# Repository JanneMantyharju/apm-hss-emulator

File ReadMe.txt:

This repository contains sources for Ardupilot Mega to Hitec telemetry adapter
For more information see: http://wp.me/p12J9M-3M

Files in this repository:
adapter/ - Source files, compile with Arduino
libraries/ - Mavlink and support libraries
hss.sch - Schematics in Eagle format
hss.brd - Board in Eagle format

Compile to ATMega328p with 8MHz clock setting.

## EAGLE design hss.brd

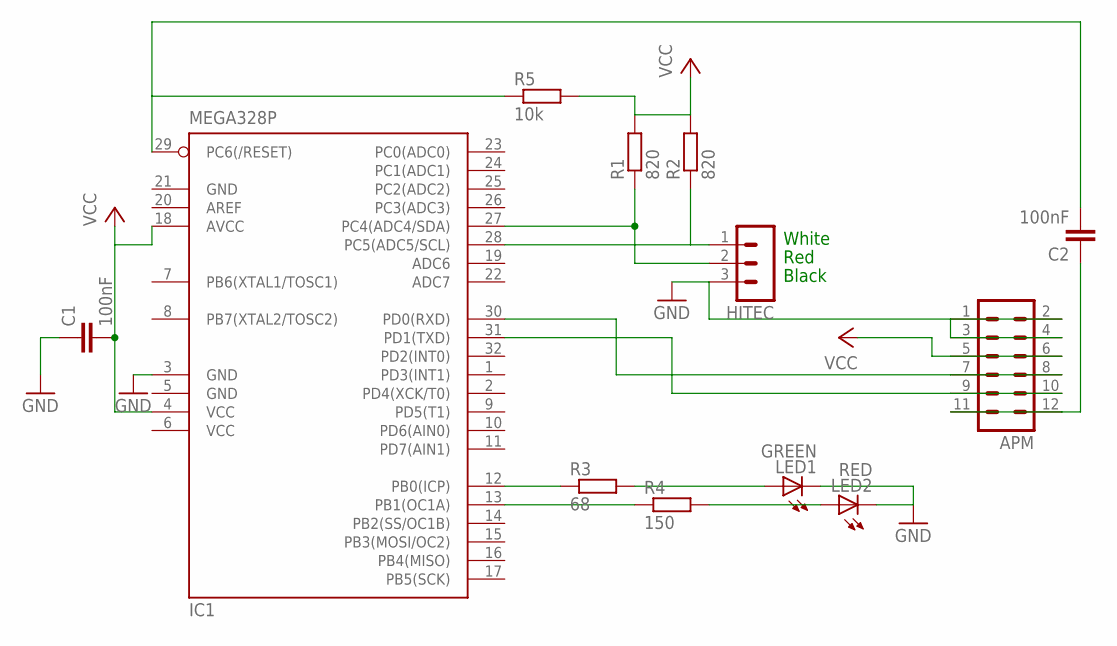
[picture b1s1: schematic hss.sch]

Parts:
APM: MA06-2
C1, C2: 100nF; C1206
HITEC: MA03-1
IC1: MEGA328P; TQFP32-08
LED1: GREEN; 1206
LED2: RED; 1206
R1, R2: 820; M1206
R3: 68; M1206
R4: 150; M1206
R5: 10k; M1206

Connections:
GND: APM.1, APM.2, APM.3, APM.4, C1.1, HITEC.3, IC1.3 (GND), IC1.5 (GND), IC1.21 (GND), LED1.C, LED2.C
unnamed: IC1.12 (PB0(ICP)), R3.1
unnamed: HITEC.2, IC1.27 (PC4(ADC4/SDA)), R1.1
unnamed: HITEC.1, IC1.28 (PC5(ADC5/SCL)), R2.1
unnamed: C2.2, IC1.29 (PC6(/RESET)), R5.1
unnamed: LED1.A, R3.2
unnamed: IC1.13 (PB1(OC1A)), R4.1
unnamed: LED2.A, R4.2
unnamed: APM.11, APM.12, C2.1
unnamed: APM.9, APM.10, IC1.31 (PD1(TXD))
unnamed: APM.7, APM.8, IC1.30 (PD0(RXD))
VCC: APM.5, APM.6, C1.2, IC1.4 (VCC), IC1.6 (VCC), IC1.18 (AVCC), R1.2, R2.2, R5.2

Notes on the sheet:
White
Red
Black

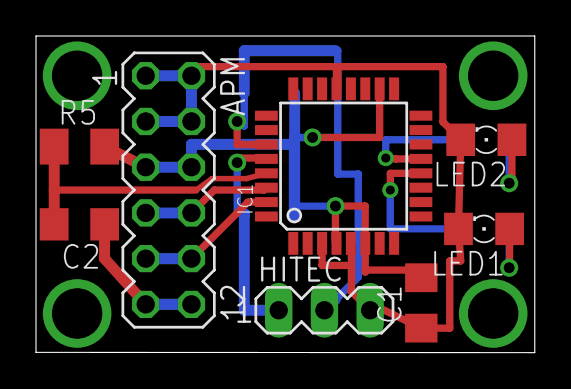
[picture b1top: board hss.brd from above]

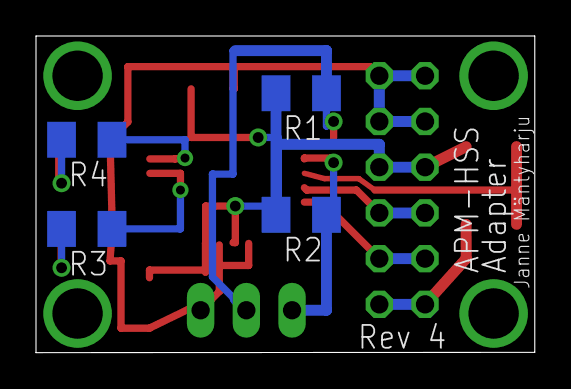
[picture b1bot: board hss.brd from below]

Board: 2 copper layers, 27.7 x 17.6 mm, 12 parts (4 on the bottom side), 12 nets.

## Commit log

2012-05-10 Support for APM2 GPS coordinates are now also shown
2012-07-13 Ported patch to work with APM version 2.40. Fixed voltage display Added ability to start the video transmitter only after gps lock has been achieved
2012-09-21 * Updated patch to work with APM 2.63 * Updated makefile and source to compile with Arduino 1.0
2012-10-14 Fixed airspeed reading
2013-01-03 Removed old patch file
2013-01-05 Updated to ArduPlane 2.69
2013-02-28 Third iteration of APM adapter
2013-03-25 Corrected schematic & board
2013-04-04 * Phanged throttle to rpm 2 and airspeed to temp 2 * Added rolling average filter to vario (climb) reading * Home altitude is now substracted from gps altitude
2015-08-31 I2C improvement
2015-09-27 version 4 of the board
